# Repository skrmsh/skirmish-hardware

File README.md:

# Skirmish Hardware

## Components

### Phaser (1st Prototype)

### Hitpoint (1st Prototype)

![Image showing a rendering of the hitpoint 
pcb](hitpoint-proto-v1/photos/rendering.png)

### Chest Module (1st Prototype)

![Image showing a rendering of the breast module 
pcb](chest-module-proto-v1/photos/rendering.png)

## License Notice

Skirmish Hardware © 2022-2023 by Ole Lange is licensed under CC BY-NC-SA 4.0.
To view a copy of this license, visit http://creativecommons.org/licenses/by-nc-sa/4.0/

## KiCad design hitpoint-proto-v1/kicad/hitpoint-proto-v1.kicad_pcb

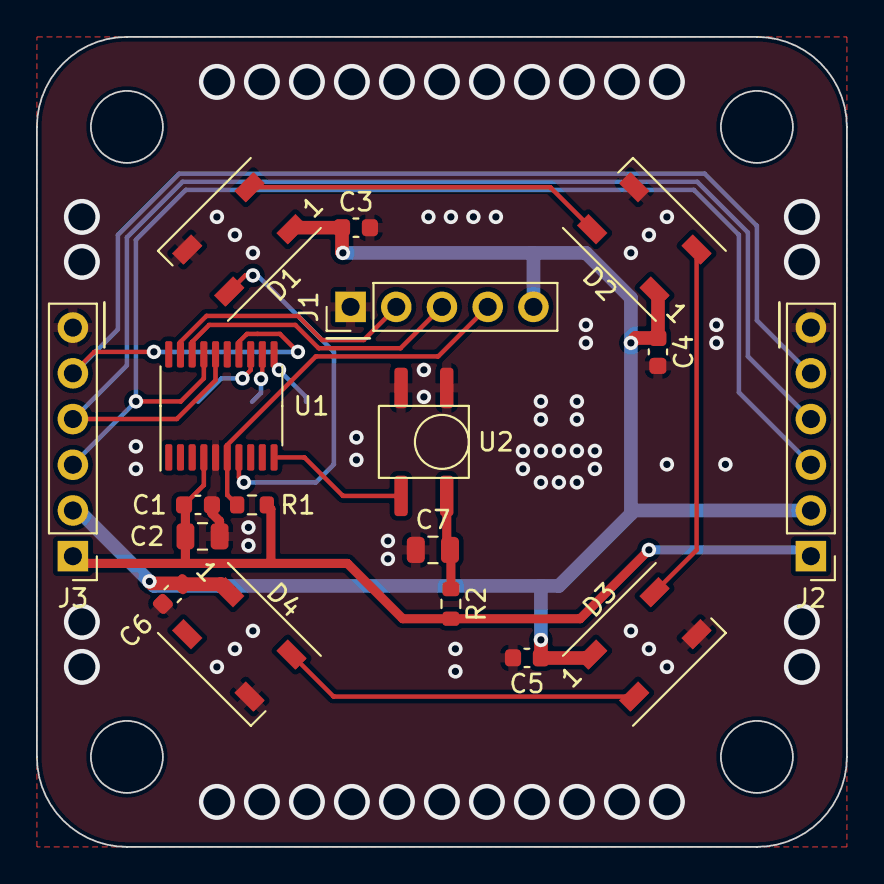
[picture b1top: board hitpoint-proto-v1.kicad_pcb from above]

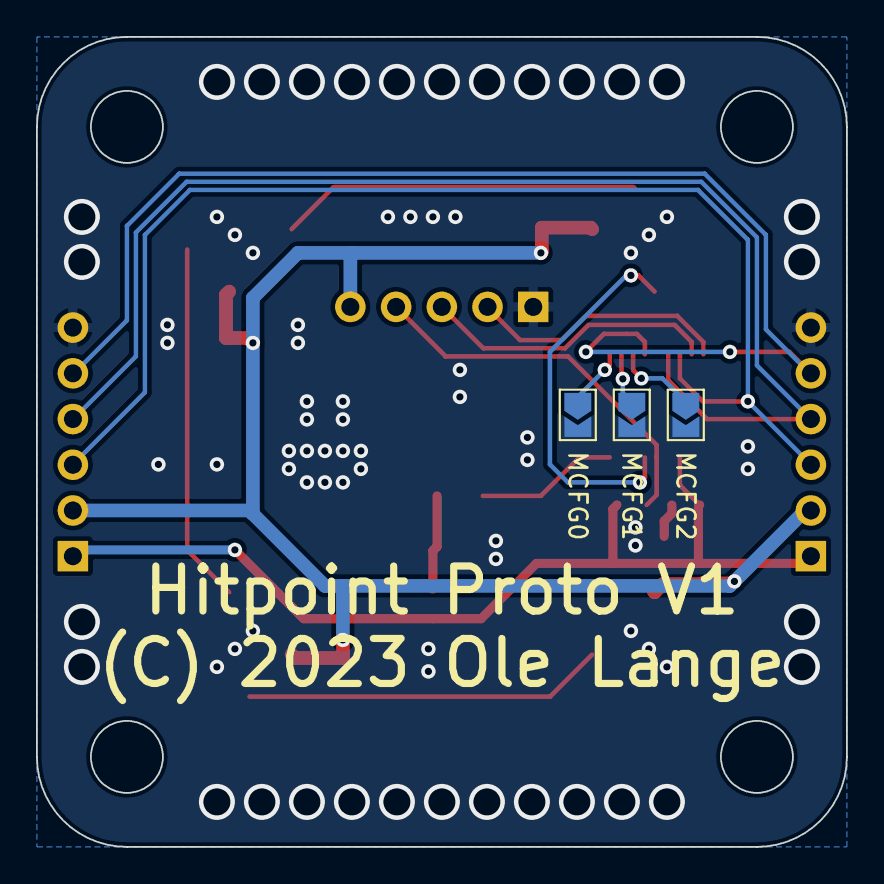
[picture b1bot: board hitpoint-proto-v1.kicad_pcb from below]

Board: 2 copper layers, 45.0 x 45.0 mm, 21 parts (3 on the bottom side), 18 nets.

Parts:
C1, C3, C4, C5, C6: 100nF; C_0603_1608Metric
C2, C7: 10uF; C_0805_2012Metric
D1, D2, D3, D4: WS2812B; LED_WS2812B_PLCC4_5.0x5.0mm_P3.2mm
J1: Conn_01x05_Male; PinHeader_1x05_P2.54mm_Vertical
J2, J3: Conn_01x06_Female; PinHeader_1x06_P2.54mm_Vertical
MCFG0, MCFG1, MCFG2: SolderJumper_2_Open; SolderJumper-2_P1.3mm_Open_TrianglePad1.0x1.5mm
R1: 10kΩ; R_0603_1608Metric
R2: 100Ω; R_0603_1608Metric
U1: STM32G030Fx; TSSOP-20_4.4x6.5mm_P0.65mm
U2: IRM-H6XXT

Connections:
+3V3: C1.1, C2.1, J2.1, J3.1, R1.1, R2.2, U1.4 (VDD/A)
+5V: C3.1, C4.1, C5.1, C6.1, D1.1 (VDD), D2.1 (VDD), D3.1 (VDD), D4.1 (VDD), J1.5, J2.2, J3.2
GND: C1.2, C2.2, C3.2, C4.2, C5.2, C6.2, C7.1, D1.3 (VSS), D2.3 (VSS), D3.3 (VSS), D4.3 (VSS), J1.1, J2.6, J3.6, MCFG0.2 (B), MCFG1.2 (B), MCFG2.2 (B), U1.5 (VSS/A), U2.1 (GND), U2.2 (GND)
I2C_IRQ: J2.5, J3.5, U1.14 (PA7)
I2C_SCL: J2.4, J3.4, U1.16 (PA11)
I2C_SDA: J2.3, J3.3, U1.17 (PA12)
IR_DATA: U1.10 (PA3), U2.3 (VOUT)
LED_DIN: D1.4 (DIN), U1.7 (PA0)
MCFG0: MCFG0.1 (A), U1.11 (PA4)
MCFG1: MCFG1.1 (A), U1.12 (PA5)
MCFG2: MCFG2.1 (A), U1.13 (PA6)
NRST: J1.4, R1.2, U1.6 (NRST)
unnamed: C7.2, R2.1, U2.4 (VCC)
unnamed: D1.2 (DOUT), D2.4 (DIN)
unnamed: D2.2 (DOUT), D3.4 (DIN)
unnamed: D3.2 (DOUT), D4.4 (DIN)
SWCLK: J1.2, U1.19 (PA15)
SWDIO: J1.3, U1.18 (PA13)

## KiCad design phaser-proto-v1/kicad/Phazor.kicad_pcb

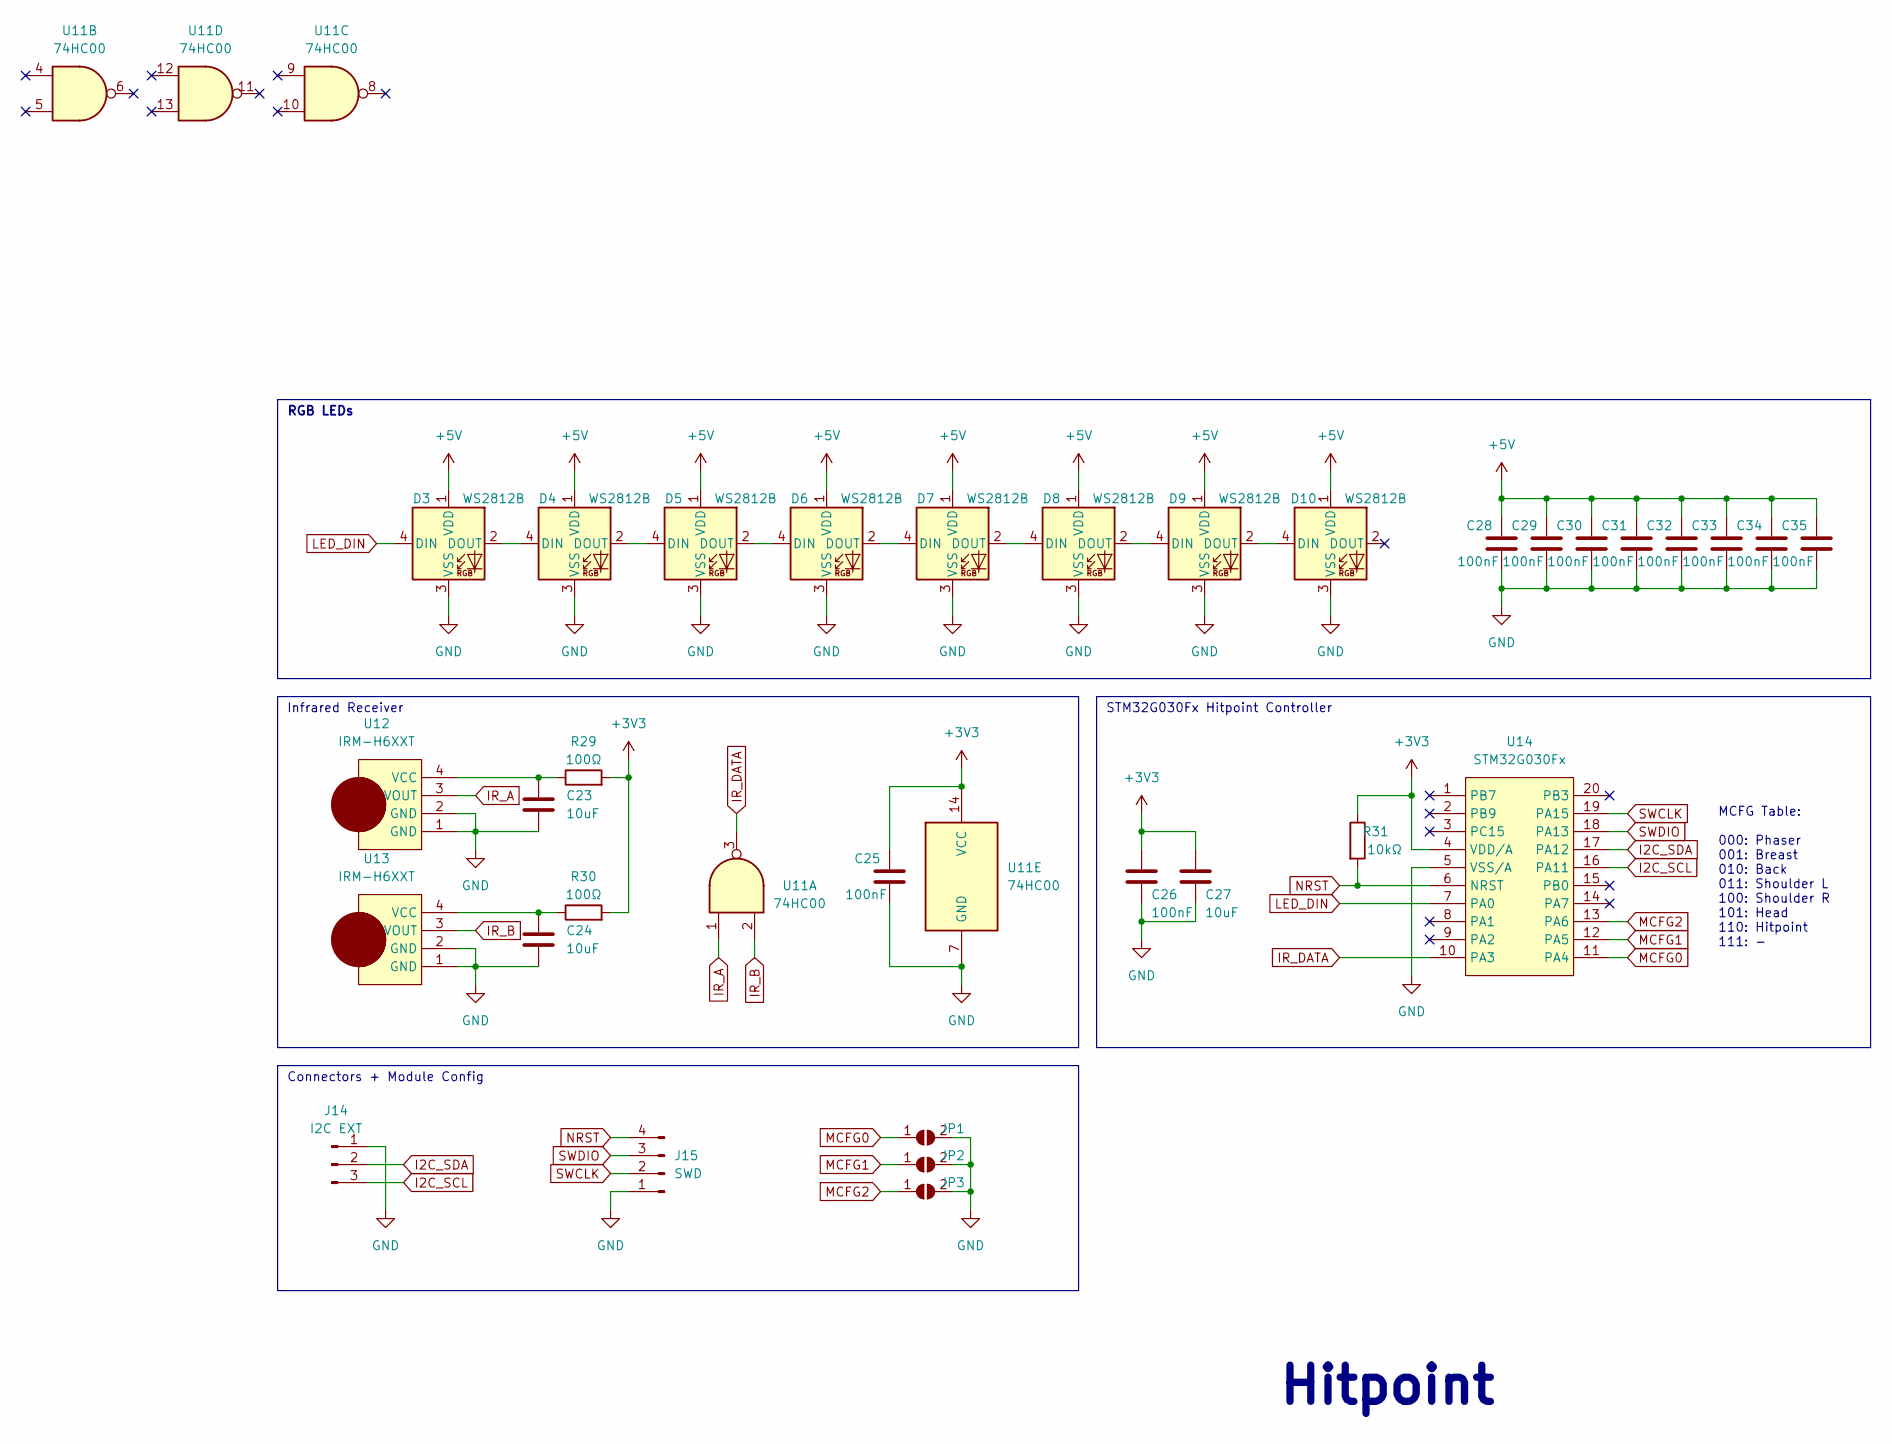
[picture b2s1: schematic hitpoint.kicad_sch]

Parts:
C23, C24, C27: 10uF; C_0805_2012Metric
C25, C26, C28, C29, C30, C31, C32, C33, C34, C35: 100nF; C_0603_1608Metric
D3, D4, D5, D6, D7, D8, D9, D10: WS2812B; LED_WS2812B_PLCC4_5.0x5.0mm_P3.2mm
J14: I2C EXT; PinSocket_1x03_P2.54mm_Vertical
J15: SWD; PinSocket_1x04_P2.54mm_Vertical
JP1, JP2, JP3: SolderJumper_2_Open; SolderJumper-2_P1.3mm_Open_TrianglePad1.0x1.5mm
R29, R30: 100Ω; R_0603_1608Metric
R31: 10kΩ; R_0603_1608Metric
U11: 74HC00; SO-14_3.9x8.65mm_P1.27mm
U12, U13: IRM-H6XXT
U14: STM32G030Fx; TSSOP-20_4.4x6.5mm_P0.65mm

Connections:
+3V3: C25.1, C26.1, C27.1, R29.2, R30.2, R31.1, U11.14 (VCC), U14.4 (VDD/A); also elsewhere on the board
+5V: C28.1, C29.1, C30.1, C31.1, C32.1, C33.1, C34.1, C35.1, D3.1 (VDD), D4.1 (VDD), D5.1 (VDD), D6.1 (VDD), D7.1 (VDD), D8.1 (VDD), D9.1 (VDD), D10.1 (VDD); also elsewhere on the board
GND: C23.1, C24.1, C25.2, C26.2, C27.2, C28.2, C29.2, C30.2, C31.2, C32.2, C33.2, C34.2, C35.2, D3.3 (VSS), D4.3 (VSS), D5.3 (VSS), D6.3 (VSS), D7.3 (VSS), D8.3 (VSS), D9.3 (VSS), D10.3 (VSS), J14.1, J15.1, JP1.2 (B), JP2.2 (B), JP3.2 (B), U11.7 (GND), U12.1 (GND), U12.2 (GND), U13.1 (GND), U13.2 (GND), U14.5 (VSS/A); also elsewhere on the board
I2C_SCL: J14.3, U14.16 (PA11); also elsewhere on the board
I2C_SDA: J14.2, U14.17 (PA12); also elsewhere on the board
IR_A: U11.1, U12.3 (VOUT)
IR_B: U11.2, U13.3 (VOUT)
IR_DATA: U11.3, U14.10 (PA3)
LED_DIN: D3.4 (DIN), U14.7 (PA0)
MCFG0: JP1.1 (A), U14.11 (PA4)
MCFG1: JP2.1 (A), U14.12 (PA5)
MCFG2: JP3.1 (A), U14.13 (PA6)
NRST: J15.4, R31.2, U14.6 (NRST)
unnamed: C23.2, R29.1, U12.4 (VCC)
unnamed: C24.2, R30.1, U13.4 (VCC)
unnamed: D3.2 (DOUT), D4.4 (DIN)
unnamed: D4.2 (DOUT), D5.4 (DIN)
unnamed: D5.2 (DOUT), D6.4 (DIN)
unnamed: D6.2 (DOUT), D7.4 (DIN)
unnamed: D7.2 (DOUT), D8.4 (DIN)
unnamed: D8.2 (DOUT), D9.4 (DIN)
unnamed: D9.2 (DOUT), D10.4 (DIN)
SWCLK: J15.2, U14.19 (PA15)
SWDIO: J15.3, U14.18 (PA13)

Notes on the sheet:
Hitpoint
RGB LEDs
Infrared Receiver
MCFG Table: 000: Phaser 001: Breast 010: Back 011: Shoulder L 100: Shoulder R 101: Head 110: Hitpoint 111: -
STM32G030Fx Hitpoint Controller
Connectors + Module Config

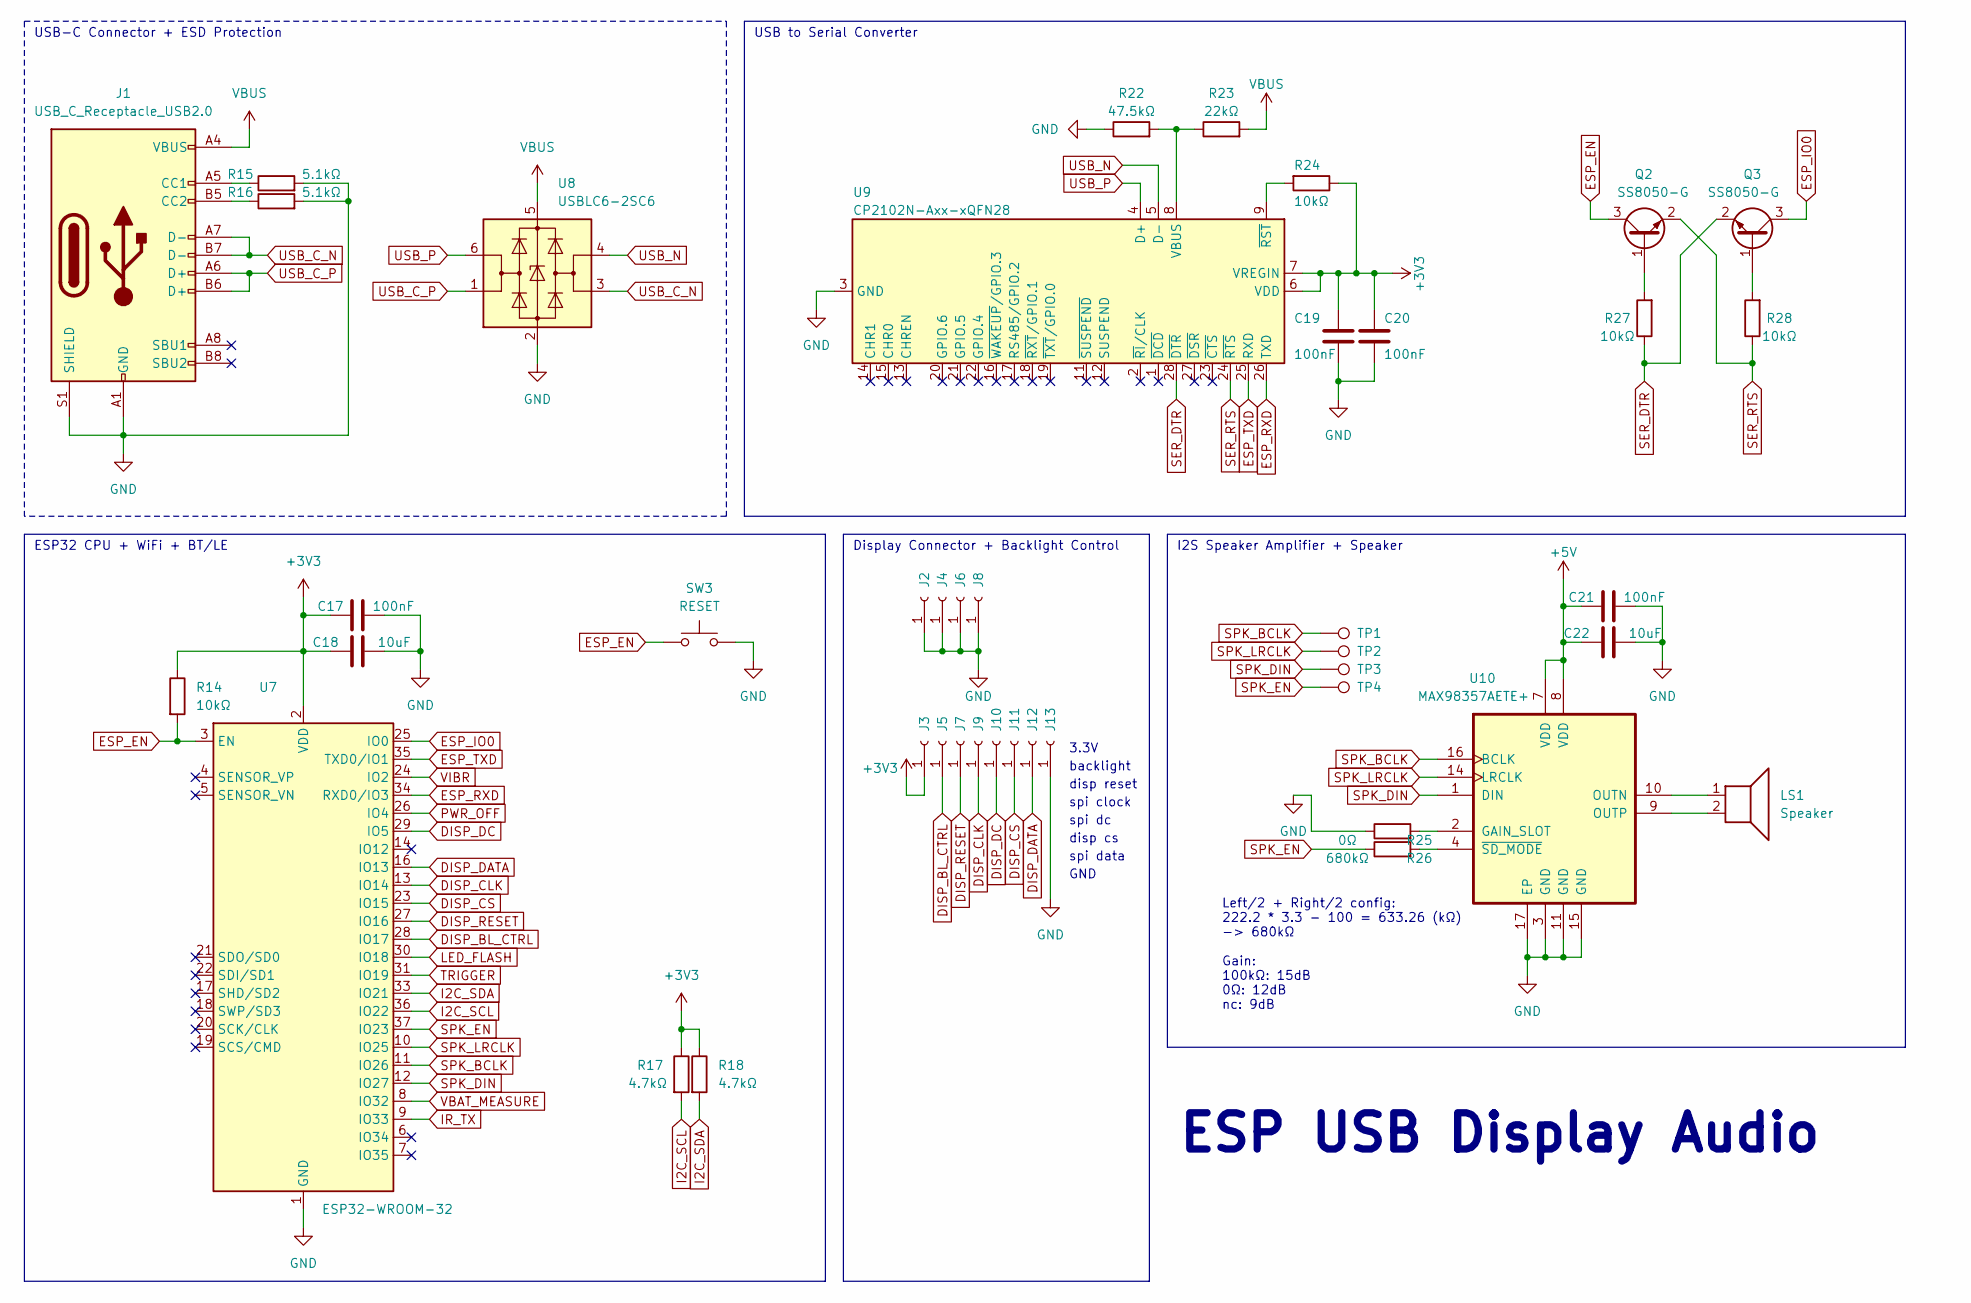
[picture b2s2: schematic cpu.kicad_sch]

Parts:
C17, C19, C20, C21: 100nF; C_0603_1608Metric
C18, C22: 10uF; C_0805_2012Metric
J1: USB_C_Receptacle_USB2.0; USB_C_Receptacle_HRO_TYPE-C-31-M-12
J2, J3, J4, J5, J6, J7, J8, J9, J10, J11, J12, J13: Conn_01x01_Female; TestPoint_Pad_2.0x2.0mm
LS1: Speaker; PinSocket_1x02_P2.54mm_Vertical
Q2, Q3: SS8050-G; SOT-23
R14, R24, R27, R28: 10kΩ; R_0603_1608Metric
R15, R16: 5.1kΩ; R_0603_1608Metric
R17, R18: 4.7kΩ; R_0603_1608Metric
R22: 47.5kΩ; R_0603_1608Metric
R23: 22kΩ; R_0603_1608Metric
R25: 0Ω; R_0603_1608Metric
R26: 680kΩ; R_0603_1608Metric
SW3: RESET; SW_Push_1P1T_NO_6x6mm_H9.5mm
TP1, TP2, TP3, TP4: TestPoint; TestPoint_Pad_D1.5mm
U7: ESP32-WROOM-32
U8: USBLC6-2SC6; SOT-23-6
U9: CP2102N-Axx-xQFN28; QFN-28-1EP_5x5mm_P0.5mm_EP3.35x3.35mm
U10: MAX98357AETE+; TQFN-16-1EP_3x3mm_P0.5mm_EP1.23x1.23mm

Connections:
+3V3: C17.1, C18.1, C19.2, C20.2, J3.1, R14.1, R17.1, R18.1, R24.1, U7.2 (VDD), U9.6 (VDD), U9.7 (VREGIN); also elsewhere on the board
+5V: C21.1, C22.1, U10.7 (VDD), U10.8 (VDD); also elsewhere on the board
DISP_BL_CTRL: J5.1, U7.28 (IO17)
DISP_CLK: J9.1, U7.13 (IO14)
DISP_CS: J11.1, U7.23 (IO15)
DISP_DATA: J12.1, U7.16 (IO13)
DISP_DC: J10.1, U7.29 (IO5)
DISP_RESET: J7.1, U7.27 (IO16)
ESP_EN: Q2.3 (C), R14.2, SW3.1, U7.3 (EN)
ESP_IO0: Q3.3 (C), U7.25 (IO0)
ESP_RXD: U7.34 (RXD0/IO3), U9.26 (TXD)
ESP_TXD: U7.35 (TXD0/IO1), U9.25 (RXD)
GND: C17.2, C18.2, C19.1, C20.1, C21.2, C22.2, J1.A1 (GND), J1.A12 (GND), J1.B1 (GND), J1.B12 (GND), J1.S1 (SHIELD), J2.1, J4.1, J6.1, J8.1, J13.1, R15.2, R16.2, R22.1, R25.1, SW3.2, U7.1 (GND), U7.15 (GND), U7.38 (GND), U7.39 (GND), U8.2 (GND), U9.3 (GND), U9.29 (GND), U10.3 (GND), U10.11 (GND), U10.15 (GND), U10.17 (EP); also elsewhere on the board
I2C_SCL: R17.2, U7.36 (IO22); also elsewhere on the board
I2C_SDA: R18.2, U7.33 (IO21); also elsewhere on the board
IR_TX: U7.9 (IO33); also elsewhere on the board
LED_FLASH: U7.30 (IO18)
unnamed: J1.A5 (CC1), R15.1
unnamed: J1.B5 (CC2), R16.1
unnamed: LS1.1, U10.10 (OUTN)
unnamed: LS1.2, U10.9 (OUTP)
unnamed: Q2.1 (B), R27.2
unnamed: Q3.1 (B), R28.2
unnamed: R22.2, R23.1, U9.8 (VBUS)
unnamed: R24.2, U9.9 (~RST)
unnamed: R25.2, U10.2 (GAIN_SLOT)
unnamed: R26.2, U10.4 (~SD_MODE)
PWR_OFF: U7.26 (IO4); also elsewhere on the board
SER_DTR: Q3.2 (E), R27.1, U9.28 (~DTR)
SER_RTS: Q2.2 (E), R28.1, U9.24 (~RTS)
SPK_BCLK: TP1.1, U7.11 (IO26), U10.16 (BCLK)
SPK_DIN: TP3.1, U7.12 (IO27), U10.1 (DIN)
SPK_EN: R26.1, TP4.1, U7.37 (IO23)
SPK_LRCLK: TP2.1, U7.10 (IO25), U10.14 (LRCLK)
TRIGGER: U7.31 (IO19); also elsewhere on the board
USB_C_N: J1.A7 (D-), J1.B7 (D-), U8.3 (I/O2)
USB_C_P: J1.A6 (D+), J1.B6 (D+), U8.1 (I/O1)
USB_N: U8.4 (I/O2), U9.5 (D-)
USB_P: U8.6 (I/O1), U9.4 (D+)
VBAT_MEASURE: U7.8 (IO32); also elsewhere on the board
VBUS: J1.A4 (VBUS), J1.A9 (VBUS), J1.B4 (VBUS), J1.B9 (VBUS), R23.2, U8.5 (VBUS); also elsewhere on the board
VIBR: U7.24 (IO2); also elsewhere on the board

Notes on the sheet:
spi dc
Display Connector + Backlight Control
disp reset
GND
3.3V
ESP32 CPU + WiFi + BT/LE
ESP USB Display Audio
backlight
spi data
I2S Speaker Amplifier + Speaker
spi clock
USB-C Connector + ESD Protection
USB to Serial Converter
Left/2 + Right/2 config: 222.2 * 3.3 - 100 = 633.26 (kΩ) -> 680kΩ Gain: 100kΩ: 15dB 0Ω: 12dB nc: 9dB
disp cs

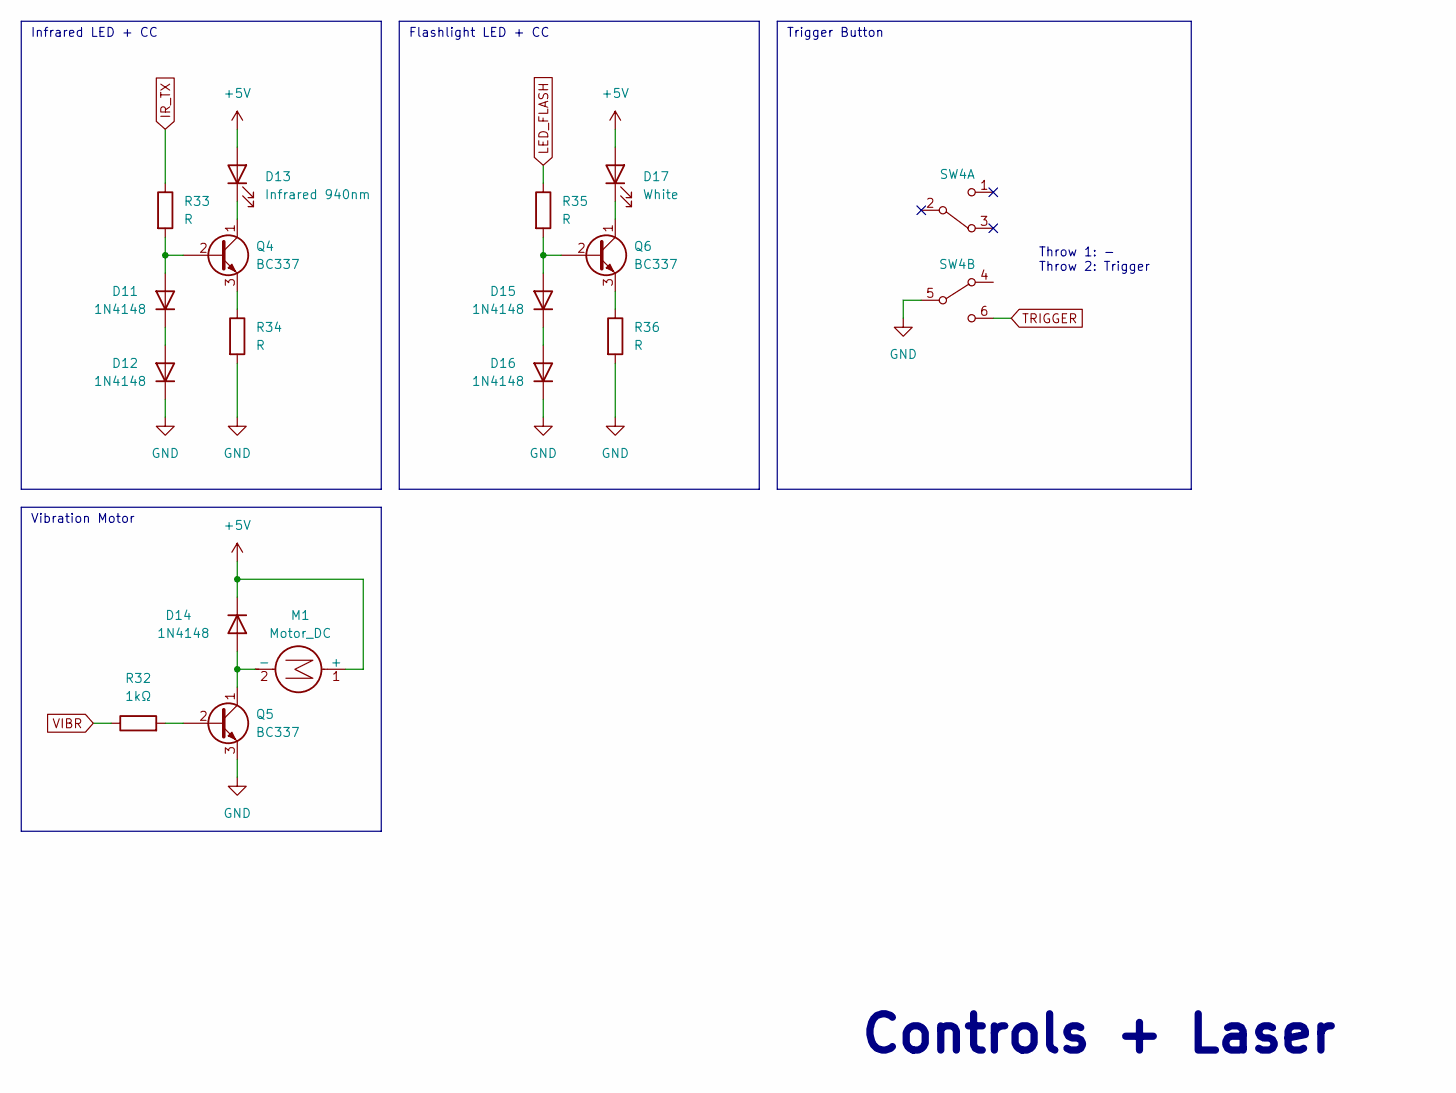
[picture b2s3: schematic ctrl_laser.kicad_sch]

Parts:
D11, D12, D14, D15, D16: 1N4148; D_SOD-123
D13: Infrared 940nm; LED_EDGE
D17: White; LED_EDGE
M1: Motor_DC; PinHeader_2x01_P2.54mm_Vertical
Q4, Q5, Q6: BC337; TO-92L_Inline_Wide
R32: 1kΩ; R_0603_1608Metric
R33, R34, R35, R36: R; R_0603_1608Metric
SW4: SW_DPDT_x2; XKB8585-Z-220-EDGE

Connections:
+5V: D13.2 (A), D14.1 (K), D17.2 (A), M1.1 (+); also elsewhere on the board
GND: D12.1 (K), D16.1 (K), Q5.3 (E), R34.2, R36.2, SW4.5 (B); also elsewhere on the board
IR_TX: R33.1; also elsewhere on the board
unnamed: D11.1 (K), D12.2 (A)
unnamed: D11.2 (A), Q4.2 (B), R33.2
unnamed: D13.1 (K), Q4.1 (C)
unnamed: D14.2 (A), M1.2 (-), Q5.1 (C)
unnamed: D15.1 (K), D16.2 (A)
unnamed: D15.2 (A), Q6.2 (B), R35.2
unnamed: D17.1 (K), Q6.1 (C)
unnamed: Q4.3 (E), R34.1
unnamed: Q5.2 (B), R32.2
unnamed: Q6.3 (E), R36.1
TRIGGER: SW4.6 (C); also elsewhere on the board
VIBR: R32.1; also elsewhere on the board

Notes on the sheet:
Vibration Motor
Infrared LED + CC
Flashlight LED + CC
Controls + Laser
Trigger Button
Throw 1: - Throw 2: Trigger

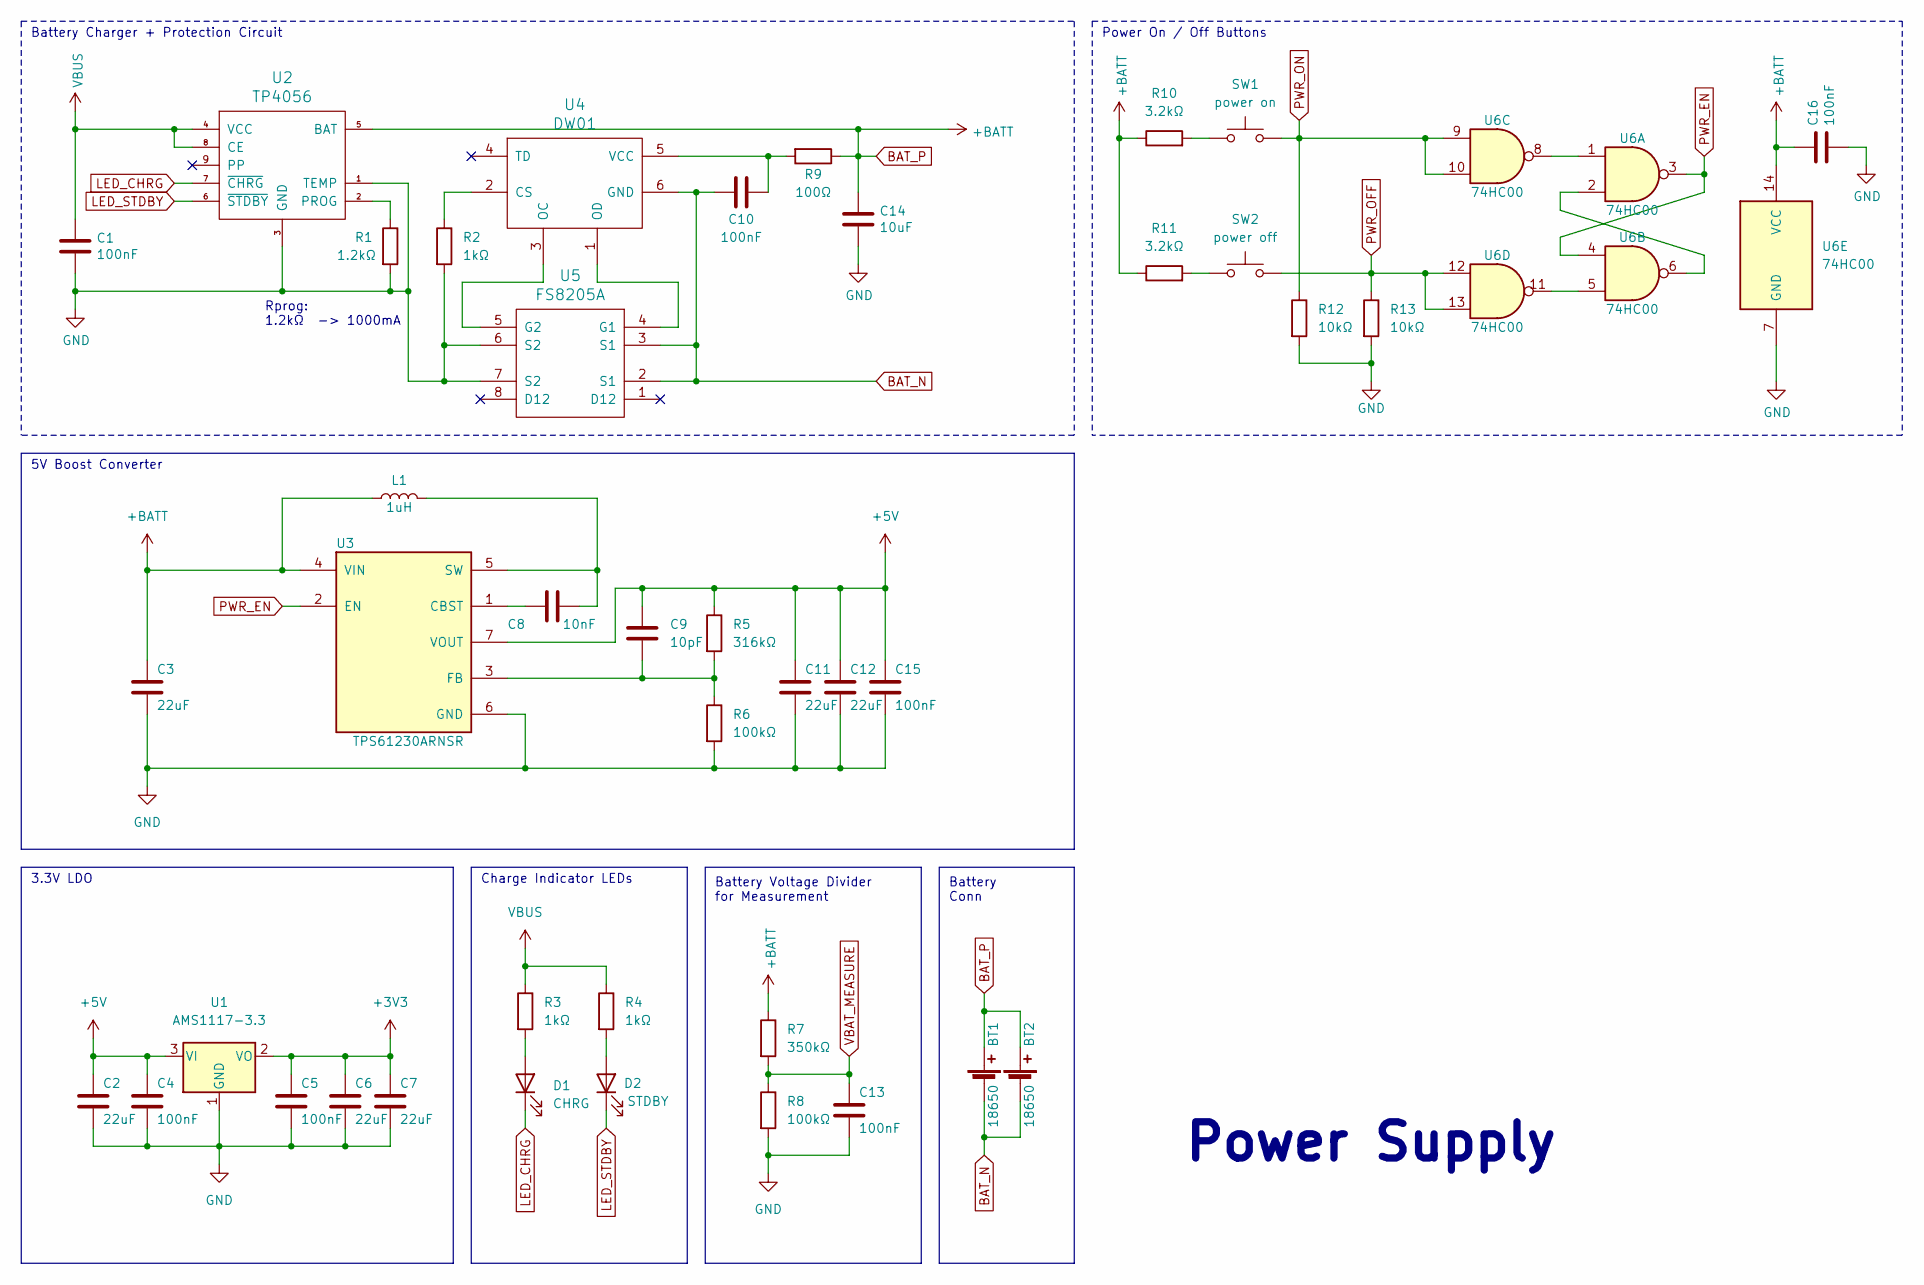
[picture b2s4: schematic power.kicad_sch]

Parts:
BT1, BT2: 18650; BatteryHolder_Keystone_1042_1x18650
C1, C4, C5, C10, C13, C15, C16: 100nF; C_0603_1608Metric
C2, C3, C6, C7, C11, C12: 22uF; C_1206_3216Metric
C8: 10nF; C_0603_1608Metric
C9: 10pF; C_0603_1608Metric
C14: 10uF; C_0805_2012Metric
D1: CHRG; LED_0603_1608Metric
D2: STDBY; LED_0603_1608Metric
L1: 1uH; L_Sunlord_MWSA0518_5.4x5.2mm
R1: 1.2kΩ; R_0603_1608Metric
R2, R3, R4: 1kΩ; R_0603_1608Metric
R5: 316kΩ; R_0603_1608Metric
R6, R8: 100kΩ; R_0603_1608Metric
R7: 350kΩ; R_0603_1608Metric
R9: 100Ω; R_0603_1608Metric
R10, R11: 3.2kΩ; R_0603_1608Metric
R12, R13: 10kΩ; R_0603_1608Metric
SW1: power on; SW_Push_1P1T_NO_6x6mm_H9.5mm
SW2: power off; SW_Push_1P1T_NO_6x6mm_H9.5mm
U1: AMS1117-3.3; SOT-223-3_TabPin2
U2: TP4056; SOIC-8-1EP_3.9x4.9mm_P1.27mm_EP2.29x3mm
U3: TPS61230ARNSR; IC_TPS61230ARNSR; PARTREV B
U4: DW01; SOT-23-6
U5: FS8205A; TSSOP-8_4.4x3mm_P0.65mm
U6: 74HC00; SO-14_3.9x8.65mm_P1.27mm

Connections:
+3V3: C5.1, C6.1, C7.1, U1.2 (VO); also elsewhere on the board
+5V: C2.1, C4.1, C9.1, C11.1, C12.1, C15.1, R5.1, U1.3 (VI), U3.7 (VOUT); also elsewhere on the board
BAT_N: BT1.2 (-), BT2.2 (-), C10.1, U4.6 (GND), U5.2 (S1), U5.3 (S1)
BAT_P: BT1.1 (+), BT2.1 (+), C3.1, C14.1, C16.1, L1.1, R7.1, R9.1, R10.1, R11.1, U2.5 (BAT), U3.4 (VIN), U6.14 (VCC)
GND: C1.2, C2.2, C3.2, C4.2, C5.2, C6.2, C7.2, C11.2, C12.2, C13.2, C14.2, C15.2, C16.2, R1.2, R2.2, R6.2, R8.2, R12.2, R13.2, U1.1 (GND), U2.1 (TEMP), U2.3 (GND), U2.9 (PP), U3.6 (GND), U5.6 (S2), U5.7 (S2), U6.7 (GND); also elsewhere on the board
LED_CHRG: D1.1 (K), U2.7 (~CHRG)
LED_STDBY: D2.1 (K), U2.6 (~STDBY)
unnamed: C8.1, U3.1 (CBST)
unnamed: C8.2, L1.2, U3.5 (SW)
unnamed: C9.2, R5.2, R6.1, U3.3 (FB)
unnamed: C10.2, R9.2, U4.5 (VCC)
unnamed: D1.2 (A), R3.2
unnamed: D2.2 (A), R4.2
unnamed: R1.1, U2.2 (PROG)
unnamed: R2.1, U4.2 (CS)
unnamed: R10.2, SW1.1
unnamed: R11.2, SW2.1
unnamed: U4.1 (OD), U5.4 (G1)
unnamed: U4.3 (OC), U5.5 (G2)
unnamed: U6.1, U6.8
unnamed: U6.2, U6.6
unnamed: U6.5, U6.11
PWR_EN: U3.2 (EN), U6.3, U6.4
PWR_OFF: R13.1, SW2.2, U6.12, U6.13; also elsewhere on the board
PWR_ON: R12.1, SW1.2, U6.9, U6.10
VBAT_MEASURE: C13.1, R7.2, R8.1; also elsewhere on the board
VBUS: C1.1, R3.1, R4.1, U2.4 (VCC), U2.8 (CE); also elsewhere on the board

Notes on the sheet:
3.3V LDO
Charge Indicator LEDs
5V Boost Converter
Battery Voltage Divider for Measurement
Battery Conn
Battery Charger + Protection Circuit
Rprog: 1.2kΩ -> 1000mA
Power On / Off Buttons
Power Supply

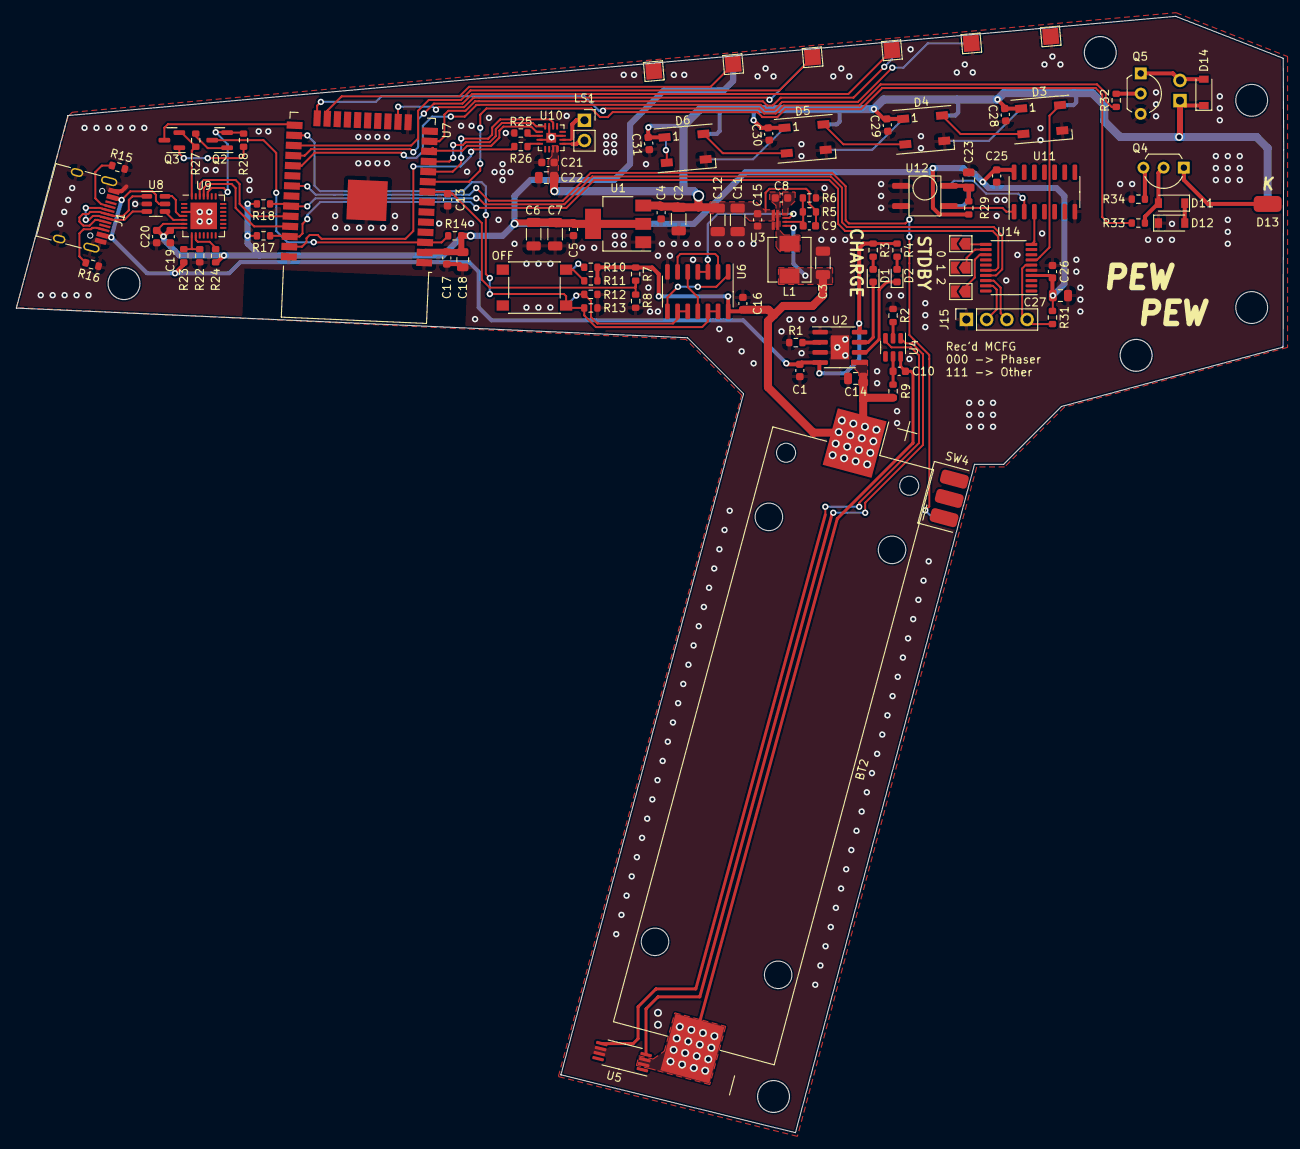
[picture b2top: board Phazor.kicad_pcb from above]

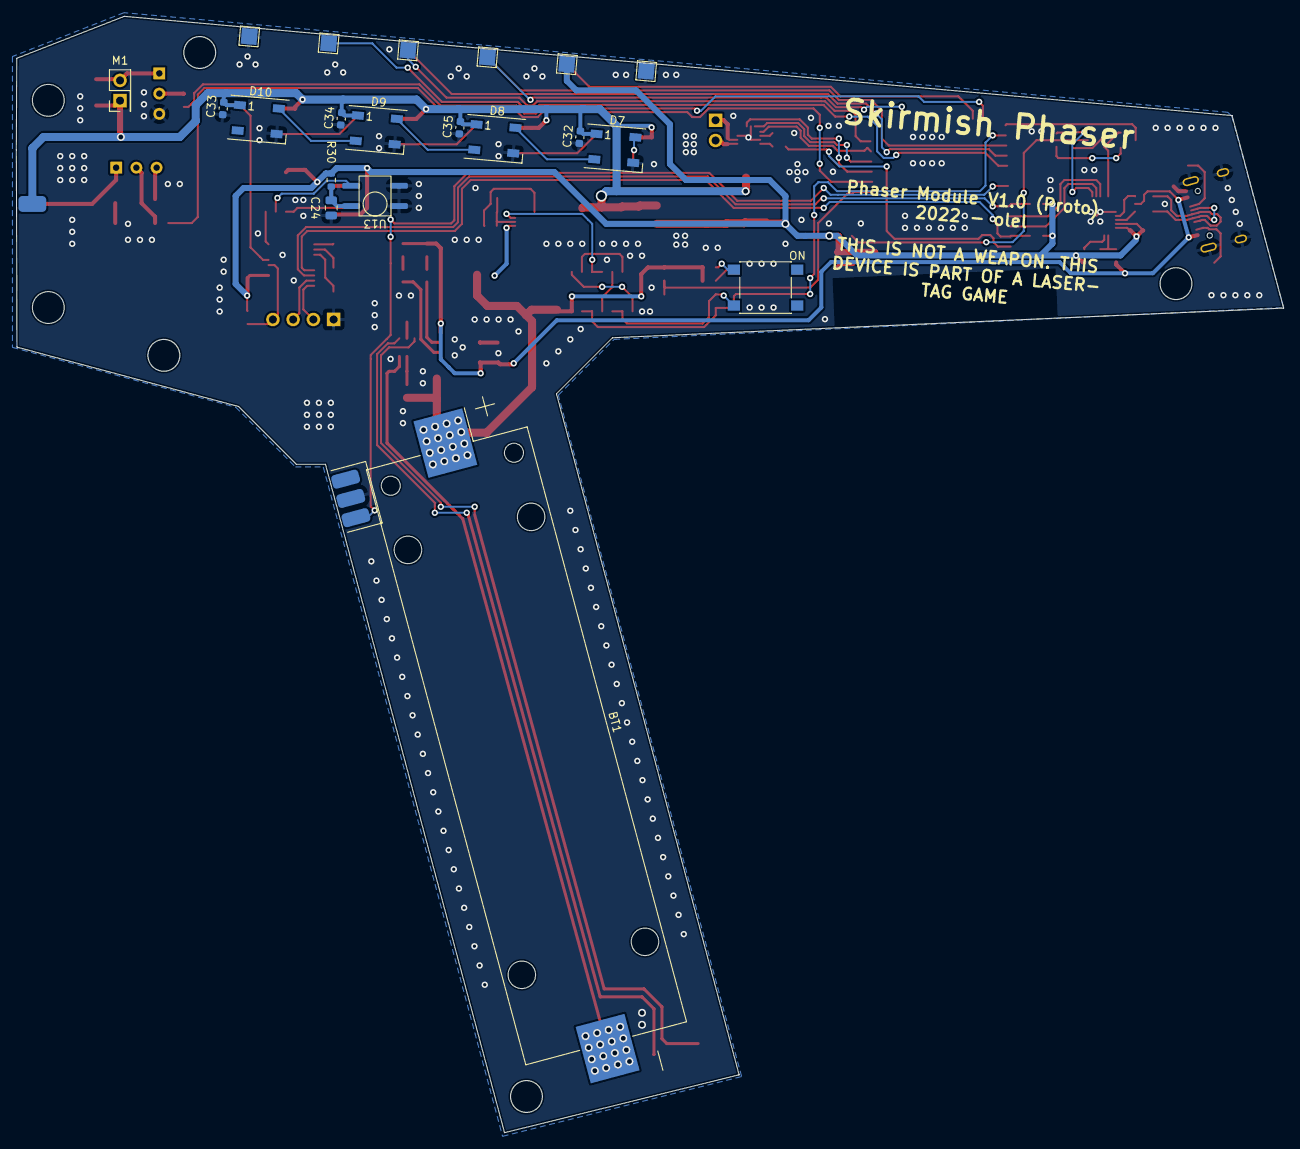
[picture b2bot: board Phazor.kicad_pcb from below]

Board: 2 copper layers, 159.0 x 140.1 mm, 123 parts (20 on the bottom side), 87 nets.

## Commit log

2023-01-20 Added gitignore file
2023-01-20 Added lense mount 3d design
2023-01-20 Added kicad project
2023-01-20 Added gerber files
2023-01-20 Added photos
2023-01-20 Added pdf schematic
2023-01-20 Added photo
2023-01-20 Added logo to readme file
2023-01-25 Schematic so far done
2023-01-28 PCB done so far
2023-01-28 Added some more ground vias
2023-01-28 Added page info
2023-01-28 Removed unused connectors from sch; added page info
2023-01-28 Changed plot dir
2023-01-28 Added gerber files zip
2023-01-28 Added rendering
2023-01-28 Added rendering to readme
2023-01-28 fix typo
2023-01-29 Parts placement done
2023-01-29 Changed battery connector footprint
2023-01-30 Rendering almost done (power rails missing)
2023-01-31 Routing finished
2023-01-31 Added gerber files + zip
2023-01-31 Added rendering of pcb
2023-01-31 Renamed strings
2023-01-31 skrmbrst to skrmvest
2023-02-01 Little mistake fixed
2023-03-29 Changed 3D models from wrl to step
2023-03-29 Added step file
2023-03-29 Minor
2023-04-19 Added license notice to readme file

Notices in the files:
breast-module-proto-v1/kicad/cpu.kicad_sch:
(C) 2023 Ole Lange
